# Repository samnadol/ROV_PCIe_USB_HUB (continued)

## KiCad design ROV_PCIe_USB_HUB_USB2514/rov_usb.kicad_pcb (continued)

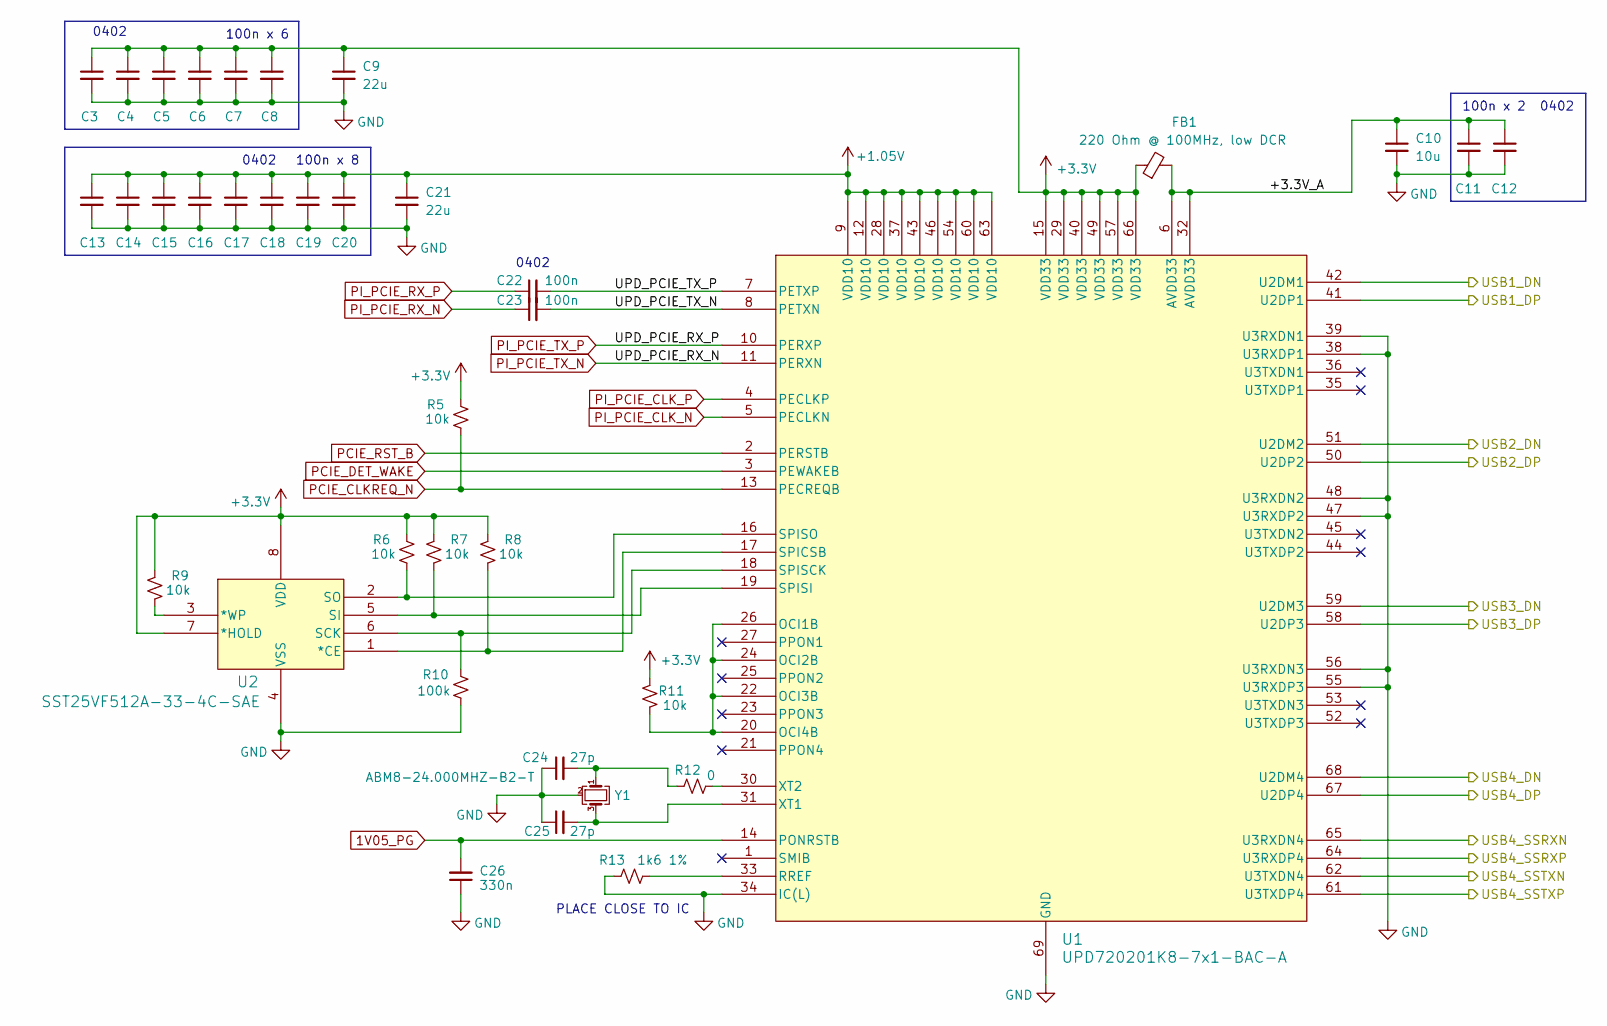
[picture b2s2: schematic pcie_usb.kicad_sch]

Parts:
C3, C4, C5, C6, C7, C8, C11, C12, C13, C14, C15, C16, C17, C18, C19, C20, C22, C23: 100n; C_0402_1005Metric; Part Number CC0402KRX7R8BB104
C9, C21: 22u; C_1206_3216Metric; Part Number CC1206KKX5R8BB226
C10: 10u; C_0805_2012Metric; Part Number CC0805KRX5R8BB106
C24, C25: 27p; C_0402_1005Metric; Part Number CC0402JRNPO9BN270
C26: 330n; C_0402_1005Metric; Part Number CC0402KPX5R6BB334
FB1: 220 Ohm @ 100MHz, low DCR; L_0805_2012Metric; Part Number BLM21PG221SN1D
R5, R6, R7, R8, R9, R11: 10k; R_0603_1608Metric; Part Number RC0603FR-0710KL
R10: 100k; R_0603_1608Metric; Part Number RC0603FR-07100KL
R12: 0; R_0402_1005Metric; Part Number RC0402JR-070RL
R13: 1k6 1%; R_0603_1608Metric; Part Number RC0603FR-071K6L
U1: UPD720201K8-7x1-BAC-A; QFN-68-1EP_8x8mm_P0.4mm_EP6.2x6.2mm
U2: SST25VF512A-33-4C-SAE; SOIC-8_3.9x4.9mm_P1.27mm
Y1: ABM8-24.000MHZ-B2-T; Crystal_SMD_3225-4Pin_3.2x2.5mm; Part Number ABM8-24.000MHZ-B2-T

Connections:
1V05_PG: C26.2, U1.14 (PONRSTB); also elsewhere on the board
+1.05V: C13.1, C14.1, C15.1, C16.1, C17.1, C18.1, C19.1, C20.1, C21.1, U1.9 (VDD10), U1.12 (VDD10), U1.28 (VDD10), U1.37 (VDD10), U1.43 (VDD10), U1.46 (VDD10), U1.54 (VDD10), U1.60 (VDD10), U1.63 (VDD10); also elsewhere on the board
+3.3V: C3.1, C4.1, C5.1, C6.1, C7.1, C8.1, C9.1, FB1.1, R5.1, R6.1, R7.1, R8.1, R9.1, R11.1, U1.15 (VDD33), U1.29 (VDD33), U1.40 (VDD33), U1.49 (VDD33), U1.57 (VDD33), U1.66 (VDD33), U2.7 (*HOLD), U2.8 (VDD); also elsewhere on the board
/PCIe_USB/+3.3V_A: C10.1, C11.1, C12.1, FB1.2, U1.6 (AVDD33), U1.32 (AVDD33)
/PCIe_USB/UPD_PCIE_TX_N: C23.2, U1.8 (PETXN)
/PCIe_USB/UPD_PCIE_TX_P: C22.2, U1.7 (PETXP)
/PCIe_USB/USB1_DN: U1.42 (U2DM1); also elsewhere on the board
/PCIe_USB/USB1_DP: U1.41 (U2DP1); also elsewhere on the board
/PCIe_USB/USB2_DN: U1.51 (U2DM2); also elsewhere on the board
/PCIe_USB/USB2_DP: U1.50 (U2DP2); also elsewhere on the board
/PCIe_USB/USB3_DN: U1.59 (U2DM3); also elsewhere on the board
/PCIe_USB/USB3_DP: U1.58 (U2DP3); also elsewhere on the board
/PCIe_USB/USB4_DN: U1.68 (U2DM4); also elsewhere on the board
/PCIe_USB/USB4_DP: U1.67 (U2DP4); also elsewhere on the board
/PCIe_USB/USB4_SSRXN: U1.65 (U3RXDN4); also elsewhere on the board
/PCIe_USB/USB4_SSRXP: U1.64 (U3RXDP4); also elsewhere on the board
/PCIe_USB/USB4_SSTXN: U1.62 (U3TXDN4); also elsewhere on the board
/PCIe_USB/USB4_SSTXP: U1.61 (U3TXDP4); also elsewhere on the board
GND: C3.2, C4.2, C5.2, C6.2, C7.2, C8.2, C9.2, C10.2, C11.2, C12.2, C13.2, C14.2, C15.2, C16.2, C17.2, C18.2, C19.2, C20.2, C21.2, C24.1, C25.1, C26.1, R10.2, R13.1, U1.34 (IC(L)), U1.38 (U3RXDP1), U1.39 (U3RXDN1), U1.47 (U3RXDP2), U1.48 (U3RXDN2), U1.55 (U3RXDP3), U1.56 (U3RXDN3), U1.69 (GND), U2.4 (VSS), Y1.2 (G), Y1.4 (G); also elsewhere on the board
unnamed: C24.2, R12.1, Y1.1
unnamed: R11.2, U1.20 (OCI4B), U1.22 (OCI3B), U1.24 (OCI2B), U1.26 (OCI1B)
unnamed: R13.2, U1.33 (RREF)
unnamed: R8.2, U1.17 (SPICSB), U2.1 (*CE)
unnamed: R10.1, U1.18 (SPISCK), U2.6 (SCK)
unnamed: R7.2, U1.19 (SPISI), U2.5 (SI)
unnamed: R6.2, U1.16 (SPISO), U2.2 (SO)
unnamed: C25.2, U1.31 (XT1), Y1.3
unnamed: R12.2, U1.30 (XT2)
unnamed: R9.2, U2.3 (*WP)
PCIE_CLKREQ_N: R5.2, U1.13 (PECREQB); also elsewhere on the board
PCIE_DET_WAKE: U1.3 (PEWAKEB); also elsewhere on the board
PCIE_RST_B: U1.2 (PERSTB); also elsewhere on the board
PI_PCIE_CLK_N: U1.5 (PECLKN); also elsewhere on the board
PI_PCIE_CLK_P: U1.4 (PECLKP); also elsewhere on the board
PI_PCIE_RX_N: C23.1; also elsewhere on the board
PI_PCIE_RX_P: C22.1; also elsewhere on the board
PI_PCIE_TX_N: U1.11 (PERXN); also elsewhere on the board
PI_PCIE_TX_P: U1.10 (PERXP); also elsewhere on the board

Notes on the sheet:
0402
100n x 6
100n x 2
PLACE CLOSE TO IC
100n x 8

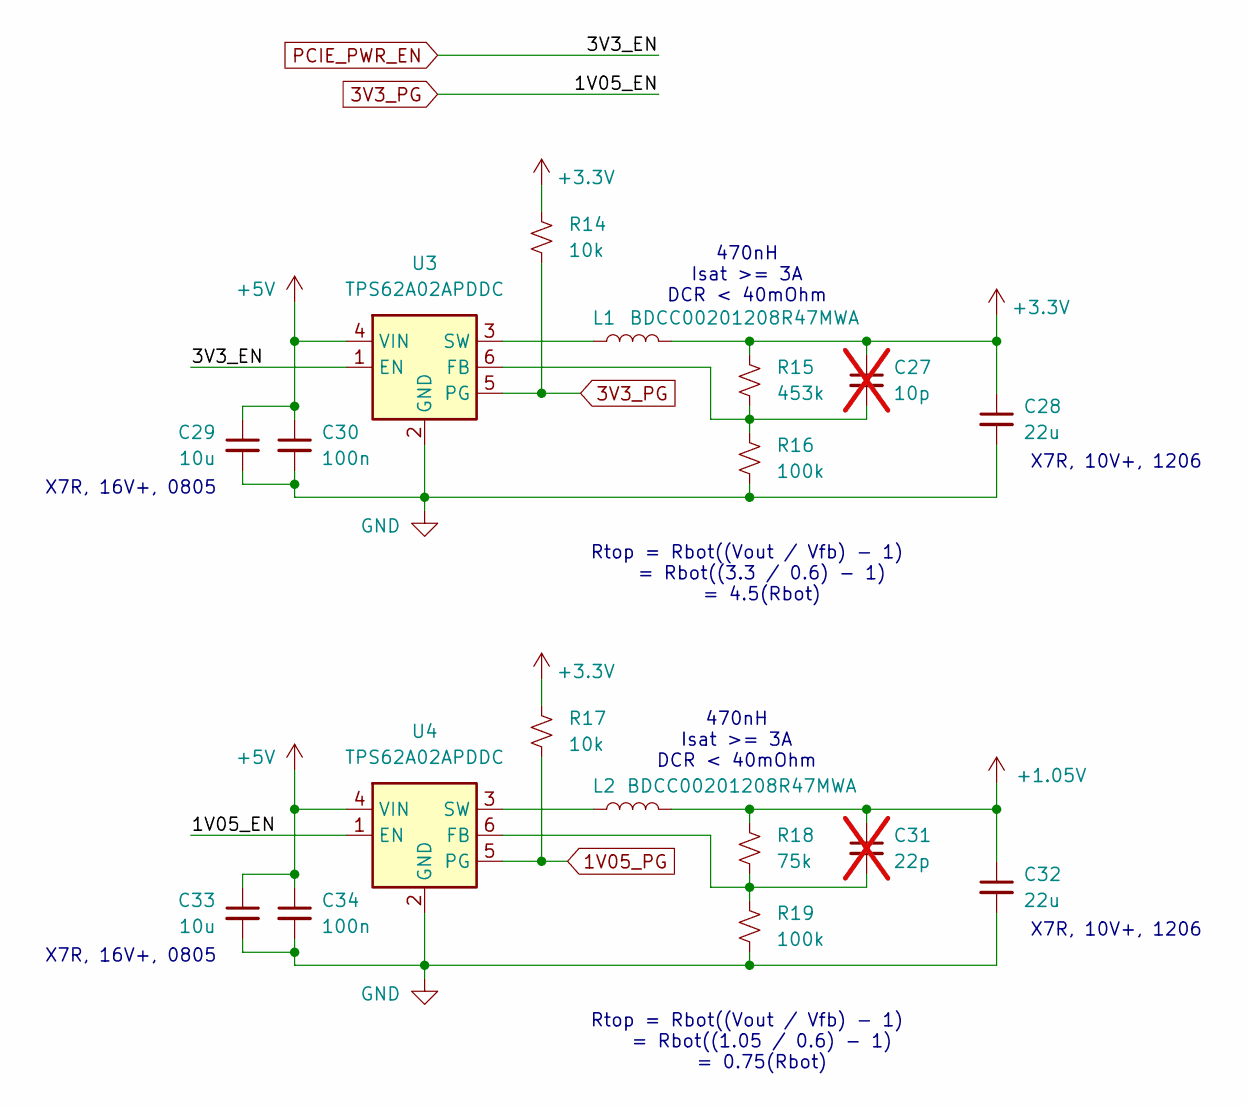
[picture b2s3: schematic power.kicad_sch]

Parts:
C27: 10p; C_0402_1005Metric; Part Number CL05C100JB5NNNC; not fitted
C28, C32: 22u; C_1206_3216Metric; Part Number CC1206KKX5R8BB226
C29, C33: 10u; C_0805_2012Metric; Part Number CC0805KRX5R8BB106
C30, C34: 100n; C_0402_1005Metric; Part Number CC0402KRX7R8BB104
C31: 22p; C_0402_1005Metric; Part Number CL05C220JB5NNNC; not fitted
L1, L2: BDCC00201208R47MWA; L_0805_2012Metric; Part Number BDCC00201208R47MWA
R14, R17: 10k; R_0603_1608Metric; Part Number RC0603FR-0710KL
R15: 453k; R_0603_1608Metric; Part Number RC0603FR-07453KL
R16, R19: 100k; R_0603_1608Metric; Part Number RC0603FR-07100KL
R18: 75k; R_0603_1608Metric; Part Number RC0603FR-0775KL
U3, U4: TPS62A02APDDC; SOT-23-6; Part Number TPS62A02APDDC

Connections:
1V05_PG: R17.2, U4.5 (PG); also elsewhere on the board
3V3_PG: R14.2, U3.5 (PG), U4.1 (EN)
+1.05V: C31.1, C32.1, L2.2, R18.1; also elsewhere on the board
+3.3V: C27.1, C28.1, L1.2, R14.1, R15.1, R17.1; also elsewhere on the board
+5V: C29.1, C30.1, C33.1, C34.1, U3.4 (VIN), U4.4 (VIN); also elsewhere on the board
GND: C28.2, C29.2, C30.2, C32.2, C33.2, C34.2, R16.2, R19.2, U3.2 (GND), U4.2 (GND); also elsewhere on the board
unnamed: C27.2, R15.2, R16.1, U3.6 (FB)
unnamed: L1.1, U3.3 (SW)
unnamed: C31.2, R18.2, R19.1, U4.6 (FB)
unnamed: L2.1, U4.3 (SW)
PCIE_PWR_EN: U3.1 (EN); also elsewhere on the board

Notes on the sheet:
X7R, 10V+, 1206
470nH Isat >= 3A DCR < 40mOhm
X7R, 16V+, 0805
Rtop = Rbot((Vout / Vfb) - 1) = Rbot((3.3 / 0.6) - 1) = 4.5(Rbot)
Rtop = Rbot((Vout / Vfb) - 1) = Rbot((1.05 / 0.6) - 1) = 0.75(Rbot)

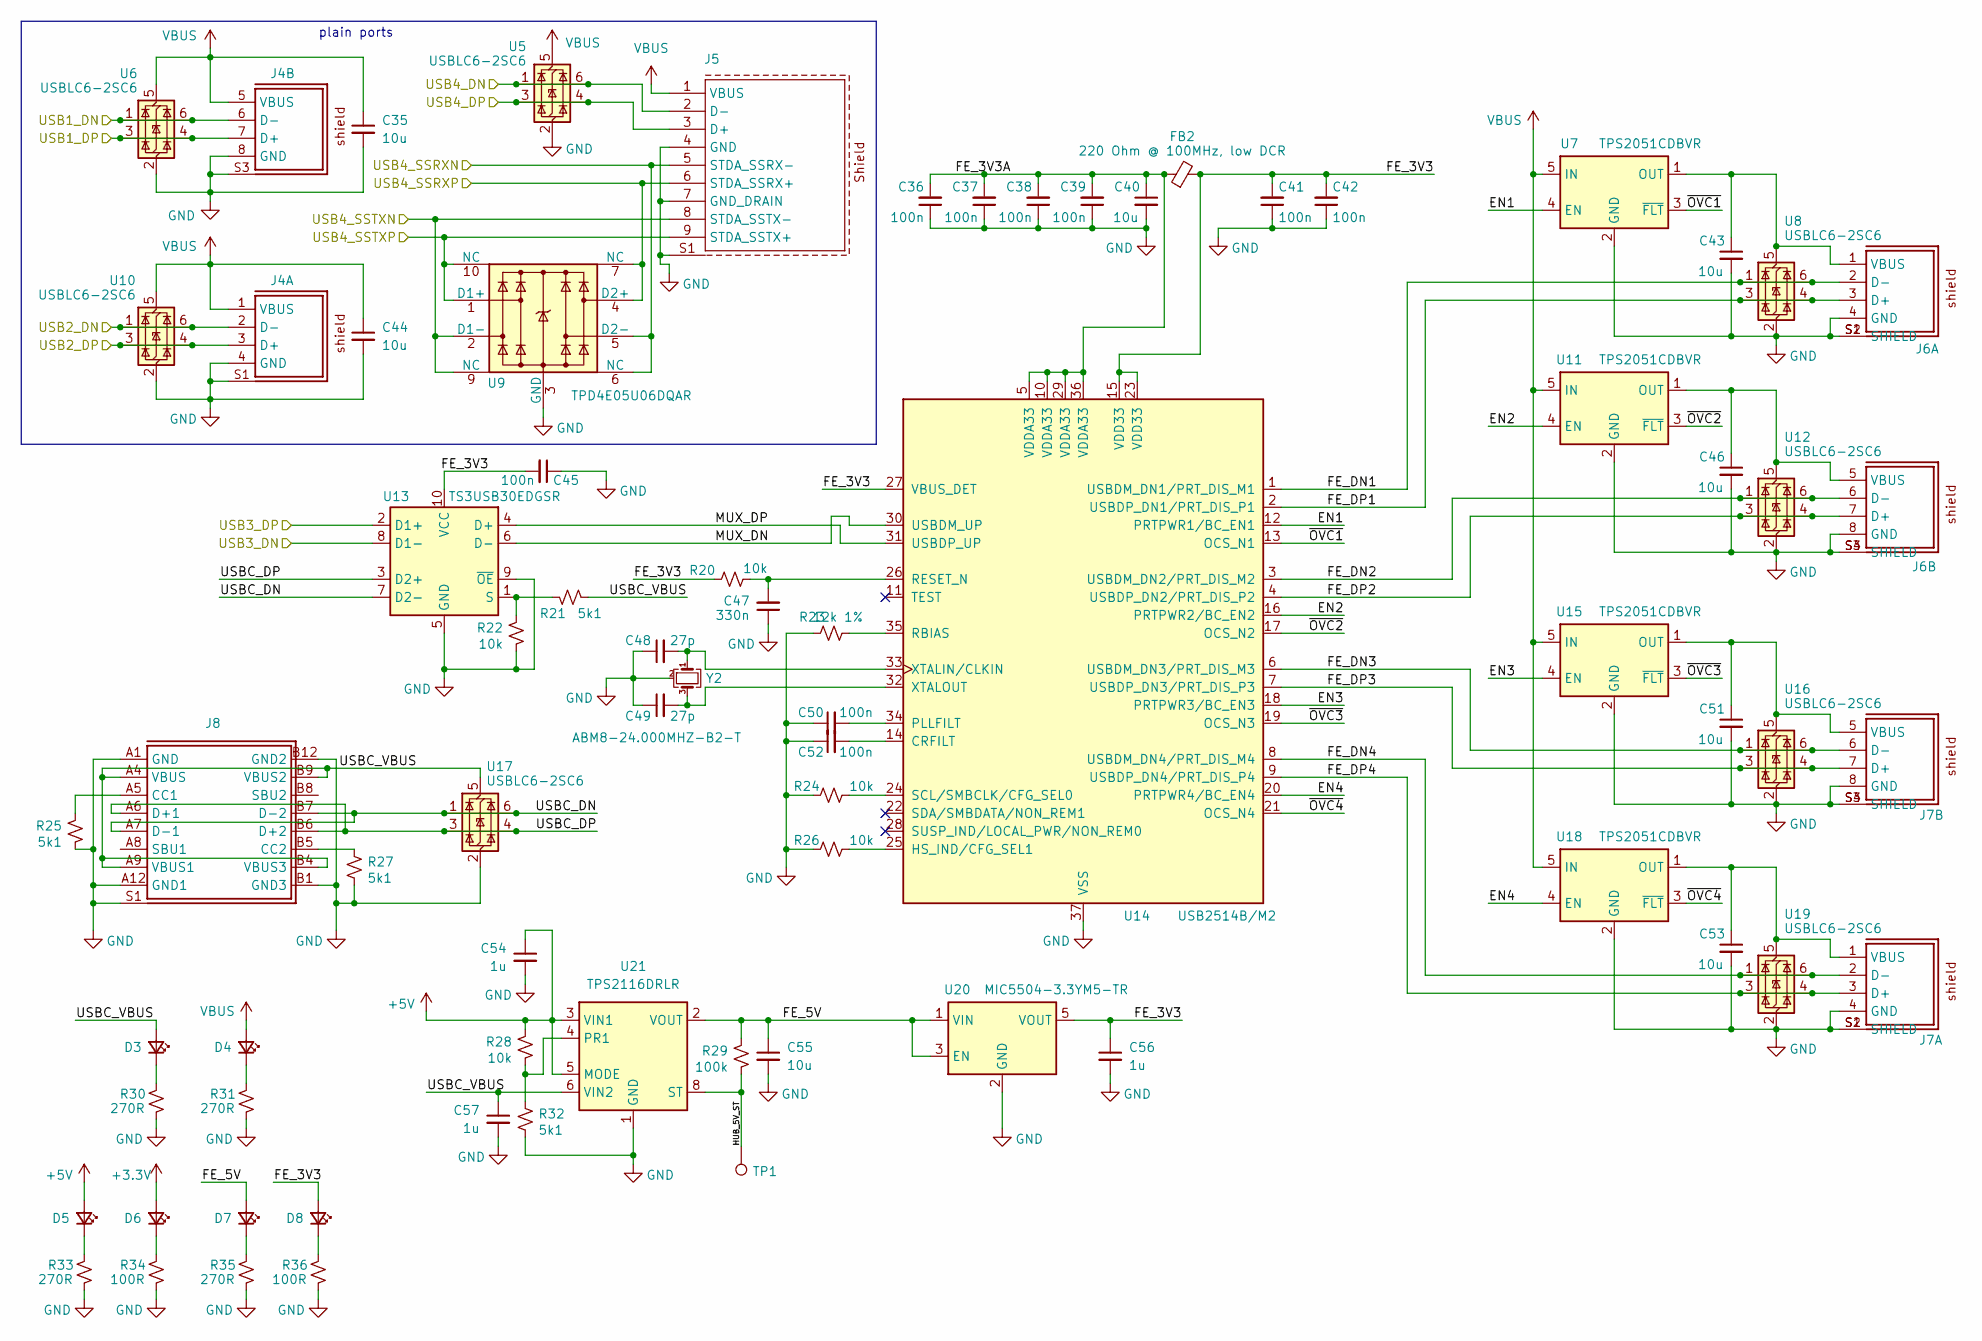
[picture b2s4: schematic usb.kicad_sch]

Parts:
C35, C40, C43, C44, C46, C51, C53, C55: 10u; C_0805_2012Metric; Part Number CC0805KRX5R8BB106
C36, C37, C38, C39, C41, C42, C45, C50, C52: 100n; C_0402_1005Metric; Part Number CC0402KRX7R8BB104
C47: 330n; C_0402_1005Metric; Part Number CC0402KPX5R6BB334
C48, C49: 27p; C_0402_1005Metric; Part Number CC0402JRNPO9BN270
C54, C56, C57: 1u; C_0603_1608Metric; Part Number CC0603KRX7R8BB105
D3, D4, D5, D6, D7, D8: Green; LED_0603_1608Metric; Part Number LTST-C190KGKT
FB2: 220 Ohm @ 100MHz, low DCR; L_0805_2012Metric; Part Number BLM21PG221SN1D
J4, J6, J7: USB-A-D-RA; J_Wurth_WR-USB_61400826021; Working Voltage (V (AC)) 30; Part Number USB-A-D-RA
J5: USB-A3-S-VT-CS5A; J_Wurth_WR-USB_692121430000; Working Voltage(V (AC)) 30 V (AC); Part Number USB-A3-S-VT-CS5A
J8: USB4085-GF-A; J_Wurth_WR-USB_629722000214; Working Voltage (V (AC)) 20; Part Number USB4085-GF-A
R20, R22, R24, R26, R28: 10k; R_0603_1608Metric; Part Number RC0603FR-0710KL
R21, R25, R27, R32: 5k1; R_0603_1608Metric; Part Number RC0603FR-075K1L
R23: 12k 1%; R_0603_1608Metric; Part Number RC0603FR-0712KL
R29: 100k; R_0603_1608Metric; Part Number RC0603FR-07100KL
R30, R31, R33, R35: 270R; R_0603_1608Metric; Part Number RC0603FR-07270RL
R34, R36: 100R; R_0603_1608Metric; Part Number RC0603FR-07100RL
TP1: TestPoint; TestPoint_Pad_1.0x1.0mm
U5, U6, U8, U10, U12, U16, U17, U19: USBLC6-2SC6; SOT-23-6; Part Number USBLC6-2SC6
U7, U11, U15, U18: TPS2051CDBVR; SOT-23-5; Part Number TPS2051CDBVR
U9: TPD4E05U06DQAR; USON-10_2.5x1.0mm_P0.5mm; Part Number TPD4E05U06DQAR
U13: TS3USB30EDGSR; TSSOP-10_3x3mm_P0.5mm; Part Number TS3USB30EDGSR
U14: USB2514B/M2; QFN-36-1EP_6x6mm_P0.5mm_EP3.7x3.7mm; Part Number USB2514B/M2
U20: MIC5504-3.3YM5-TR; SOT-23-5; Part Number MIC5504-3.3YM5-TR
U21: TPS2116DRLR; SOT-583-8; Part Number TPS2116DRLR
Y2: ABM8-24.000MHZ-B2-T; Crystal_SMD_3225-4Pin_3.2x2.5mm; Part Number ABM8-24.000MHZ-B2-T

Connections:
+3.3V: D6.2 (A); also elsewhere on the board
+5V: C54.1, D5.2 (A), R28.2, U21.3 (VIN1), U21.5 (MODE); also elsewhere on the board
/PCIe_USB/USB1_DN: J4.6 (D-), U6.1 (I/O1), U6.6 (I/O1); also elsewhere on the board
/PCIe_USB/USB1_DP: J4.7 (D+), U6.3 (I/O2), U6.4 (I/O2); also elsewhere on the board
/PCIe_USB/USB2_DN: J4.2 (D-), U10.1 (I/O1), U10.6 (I/O1); also elsewhere on the board
/PCIe_USB/USB2_DP: J4.3 (D+), U10.3 (I/O2), U10.4 (I/O2); also elsewhere on the board
/PCIe_USB/USB3_DN: U13.8 (D1-); also elsewhere on the board
/PCIe_USB/USB3_DP: U13.2 (D1+); also elsewhere on the board
/PCIe_USB/USB4_DN: J5.2 (D-), U5.1 (I/O1), U5.6 (I/O1); also elsewhere on the board
/PCIe_USB/USB4_DP: J5.3 (D+), U5.3 (I/O2), U5.4 (I/O2); also elsewhere on the board
/PCIe_USB/USB4_SSRXN: J5.5 (STDA_SSRX-), U9.5 (D2-), U9.6 (NC); also elsewhere on the board
/PCIe_USB/USB4_SSRXP: J5.6 (STDA_SSRX+), U9.4 (D2+), U9.7 (NC); also elsewhere on the board
/USB/EN1: U7.4 (EN), U14.12 (PRTPWR1/BC_EN1)
/USB/EN2: U11.4 (EN), U14.16 (PRTPWR2/BC_EN2)
/USB/EN3: U14.18 (PRTPWR3/BC_EN3), U15.4 (EN)
/USB/EN4: U14.20 (PRTPWR4/BC_EN4), U18.4 (EN)
/USB/FE_3V3: C41.2, C42.2, C45.2, C56.1, D8.2 (A), FB2.2, R20.2, U13.10 (VCC), U14.15 (VDD33), U14.23 (VDD33), U14.27 (VBUS_DET), U20.5 (VOUT)
/USB/FE_3V3A: C36.2, C37.2, C38.2, C39.2, C40.1, FB2.1, U14.5 (VDDA33), U14.10 (VDDA33), U14.29 (VDDA33), U14.36 (VDDA33)
/USB/FE_5V: C55.1, D7.2 (A), R29.2, U20.1 (VIN), U20.3 (EN), U21.2 (VOUT), U21.7 (VOUT)
/USB/FE_DN1: J6.2 (D-), U8.1 (I/O1), U8.6 (I/O1), U14.1 (USBDM_DN1/PRT_DIS_M1)
/USB/FE_DN2: J6.6 (D-), U12.1 (I/O1), U12.6 (I/O1), U14.3 (USBDM_DN2/PRT_DIS_M2)
/USB/FE_DN3: J7.6 (D-), U14.6 (USBDM_DN3/PRT_DIS_M3), U16.1 (I/O1), U16.6 (I/O1)
/USB/FE_DN4: J7.2 (D-), U14.8 (USBDM_DN4/PRT_DIS_M4), U19.1 (I/O1), U19.6 (I/O1)
/USB/FE_DP1: J6.3 (D+), U8.3 (I/O2), U8.4 (I/O2), U14.2 (USBDP_DN1/PRT_DIS_P1)
/USB/FE_DP2: J6.7 (D+), U12.3 (I/O2), U12.4 (I/O2), U14.4 (USBDP_DN2/PRT_DIS_P2)
/USB/FE_DP3: J7.7 (D+), U14.7 (USBDP_DN3/PRT_DIS_P3), U16.3 (I/O2), U16.4 (I/O2)
/USB/FE_DP4: J7.3 (D+), U14.9 (USBDP_DN4/PRT_DIS_P4), U19.3 (I/O2), U19.4 (I/O2)
/USB/HUB_5V_ST: R29.1, TP1.1 (1_1), U21.8 (ST)
/USB/MUX_DN: U13.6 (D-), U14.30 (USBDM_UP)
/USB/MUX_DP: U13.4 (D+), U14.31 (USBDP_UP)
/USB/USB4_SSTXN: J5.8 (STDA_SSTX-), U9.2 (D1-), U9.9 (NC); also elsewhere on the board
/USB/USB4_SSTXP: J5.9 (STDA_SSTX+), U9.1 (D1+), U9.10 (NC); also elsewhere on the board
/USB/USBC_DN: J8.A7 (D-1), J8.B7 (D-2), U13.7 (D2-), U17.1 (I/O1), U17.6 (I/O1)
/USB/USBC_DP: J8.A6 (D+1), J8.B6 (D+2), U13.3 (D2+), U17.3 (I/O2), U17.4 (I/O2)
/USB/USBC_VBUS: C57.1, D3.2 (A), J8.A4 (VBUS), J8.A9 (VBUS1), J8.B4 (VBUS3), J8.B9 (VBUS2), R21.1, U17.5 (VBUS), U21.6 (VIN2)
/USB/~OVC1: U7.3 (~FLT), U14.13 (OCS_N1)
/USB/~OVC2: U11.3 (~FLT), U14.17 (OCS_N2)
/USB/~OVC3: U14.19 (OCS_N3), U15.3 (~FLT)
/USB/~OVC4: U14.21 (OCS_N4), U18.3 (~FLT)
GND: C35.2, C36.1, C37.1, C38.1, C39.1, C40.2, C41.1, C42.1, C43.2, C44.2, C45.1, C46.2, C47.1, C48.1, C49.1, C50.1, C51.2, C52.1, C53.2, C54.2, C55.2, C56.2, C57.2, J4.4 (GND), J4.8 (GND), J4.S1, J4.S2, J4.S3, J4.S4, J5.4 (GND), J5.7 (GND_DRAIN), J5.S1, J5.S2 (SHIELD), J6.4 (GND), J6.8 (GND), J6.S1 (SHIELD), J6.S2 (SHIELD), J6.S3 (SHIELD), J6.S4 (SHIELD), J7.4 (GND), J7.8 (GND), J7.S1 (SHIELD), J7.S2 (SHIELD), J7.S3 (SHIELD), J7.S4 (SHIELD), J8.A1 (GND), J8.A12 (GND1), J8.B1 (GND3), J8.B12 (GND2), J8.S1, J8.S2, J8.S3, J8.S4, R22.1, R23.2, R24.2, R25.1, R26.2, R27.1, R30.1, R31.1, R32.1, R33.1, R34.1, R35.1, R36.1, U5.2 (GND), U6.2 (GND), U7.2 (GND), U8.2 (GND), U9.3 (GND), U9.8 (GND), U10.2 (GND), U11.2 (GND), U12.2 (GND), U13.5 (GND), U13.9 (~OE), U14.37 (VSS), U15.2 (GND), U16.2 (GND), U17.2 (GND), U18.2 (GND), U19.2 (GND), U20.2 (GND), U21.1 (GND), Y2.2 (G), Y2.4 (G); also elsewhere on the board
unnamed: D3.1 (K), R30.2
unnamed: D4.1 (K), R31.2
unnamed: D5.1 (K), R33.2
unnamed: D6.1 (K), R34.2
unnamed: D7.1 (K), R35.2
unnamed: D8.1 (K), R36.2
unnamed: C43.1, J6.1 (VBUS), U7.1 (OUT), U8.5 (VBUS)
unnamed: C46.1, J6.5 (VBUS), U11.1 (OUT), U12.5 (VBUS)
unnamed: C53.1, J7.1 (VBUS), U18.1 (OUT), U19.5 (VBUS)
unnamed: C51.1, J7.5 (VBUS), U15.1 (OUT), U16.5 (VBUS)
unnamed: J8.A5 (CC1), R25.2
unnamed: J8.B5 (CC2), R27.2
unnamed: R21.2, R22.2, U13.1 (S)
unnamed: C52.2, U14.14 (CRFILT)
unnamed: R26.1, U14.25 (HS_IND/CFG_SEL1)
unnamed: C50.2, U14.34 (PLLFILT)
unnamed: R23.1, U14.35 (RBIAS)
unnamed: C47.2, R20.1, U14.26 (RESET_N)
unnamed: R24.1, U14.24 (SCL/SMBCLK/CFG_SEL0)
unnamed: C48.2, U14.33 (XTALIN/CLKIN), Y2.1
unnamed: C49.2, U14.32 (XTALOUT), Y2.3
unnamed: R28.1, R32.2, U21.4 (PR1)
VBUS: C35.1, C44.1, D4.2 (A), J4.1 (VBUS), J4.5 (VBUS), J5.1 (VBUS), U5.5 (VBUS), U6.5 (VBUS), U7.5 (IN), U10.5 (VBUS), U11.5 (IN), U15.5 (IN), U18.5 (IN); also elsewhere on the board

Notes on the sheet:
plain ports

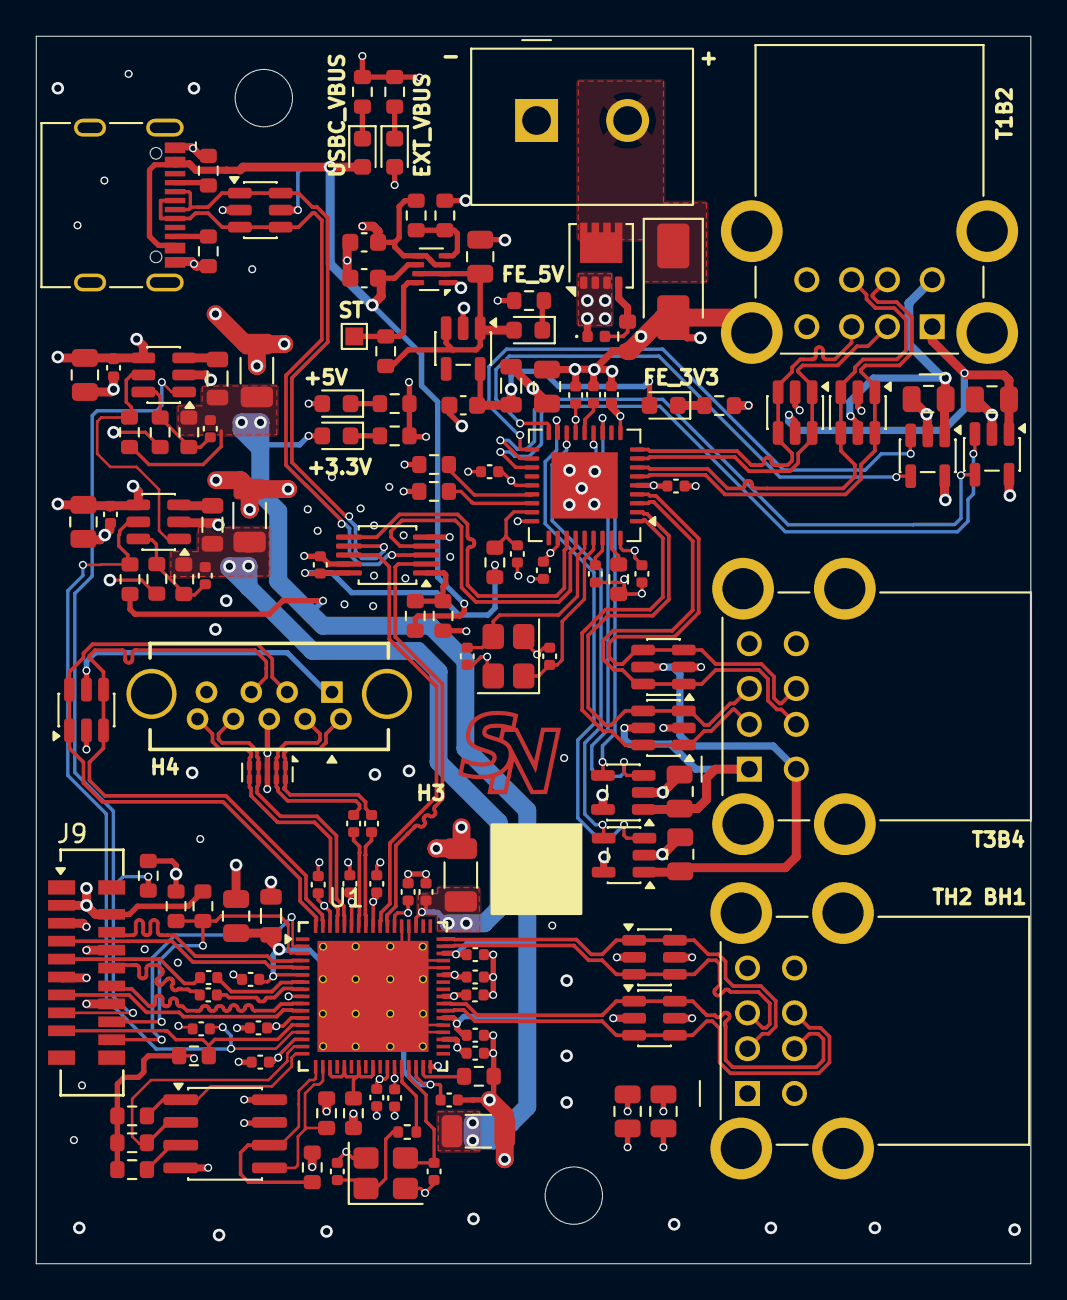
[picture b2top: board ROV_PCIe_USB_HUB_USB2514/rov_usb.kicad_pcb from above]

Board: 4 copper layers, 55.5 x 68.5 mm, 139 parts (0 on the bottom side), 97 nets.

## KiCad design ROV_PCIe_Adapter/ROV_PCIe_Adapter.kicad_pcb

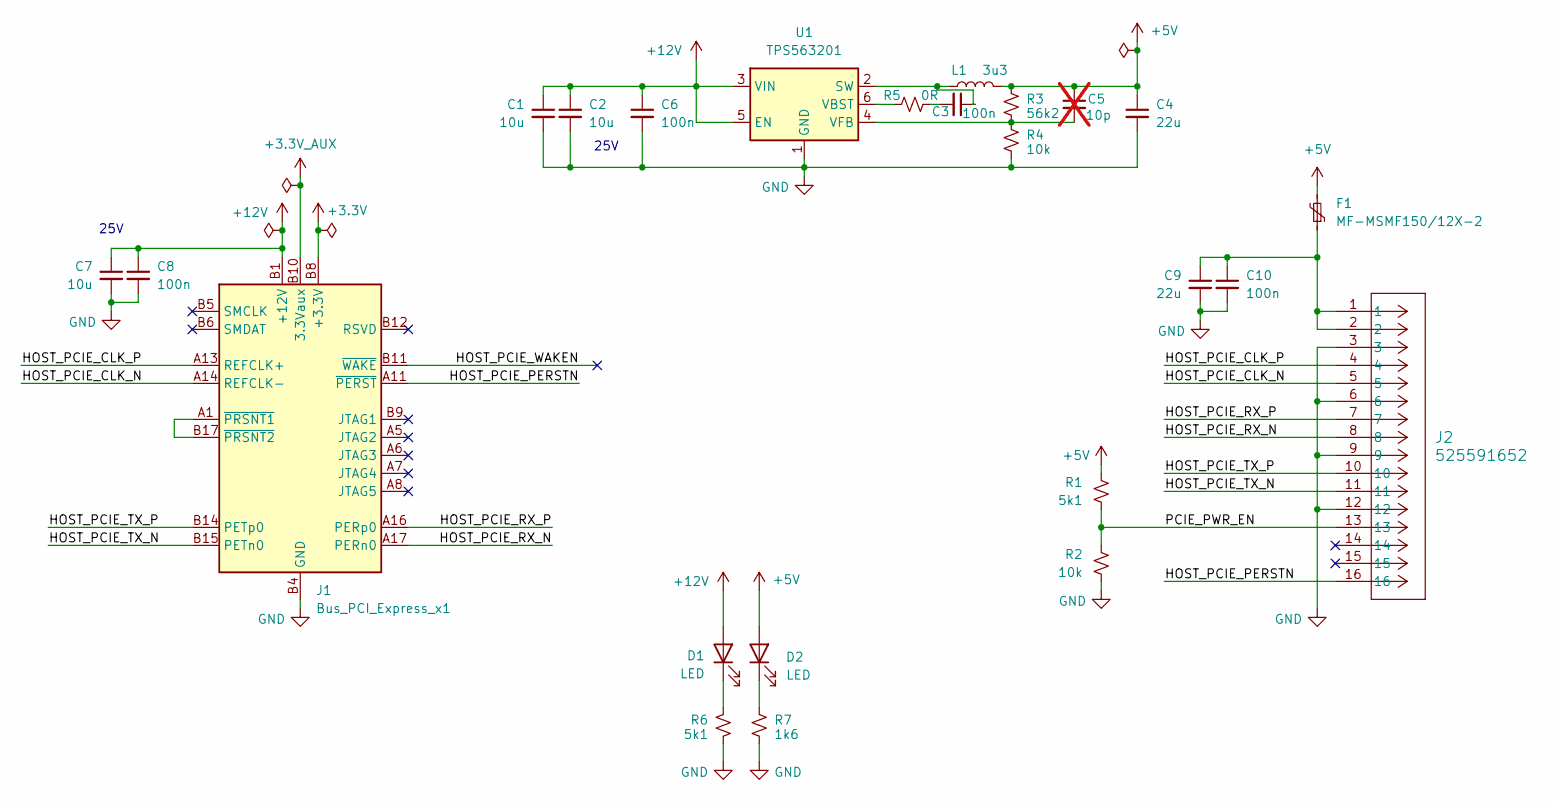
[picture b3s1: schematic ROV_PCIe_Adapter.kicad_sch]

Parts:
C1, C2, C7: 10u; C_0805_2012Metric; Voltage Rating 25; Part Number CC0805KRX5R8BB106
C3, C6, C8, C10: 100n; C_0402_1005Metric; Voltage Rating 25; Part Number CC0402KRX7R8BB104
C4, C9: 22u; C_1206_3216Metric; Voltage Rating 25; Part Number CC1206KKX5R8BB226
C5: 10p; C_0402_1005Metric; Part Number CL05A104KA5NNNC; not fitted
D1, D2: LED; LED_0603_1608Metric; Part Number LTST-C190KGKT
F1: MF-MSMF150/12X-2; Fuse_1812_4532Metric; Part Number MF-MSMF150/12X-2
J1: Bus_PCI_Express_x1; BUS_PCIexpress_x1
J2: 525591652; Part Number 525591652
L1: 3u3; L_Taiyo-Yuden_MD-5050; Part Number BWVC005050403R3M00
R1, R6: 5k1; R_0603_1608Metric; Part Number RC0603FR-075K1L
R2, R4: 10k; R_0603_1608Metric; Part Number RC0603FR-0710KL
R3: 56k2; R_0603_1608Metric; Part Number RC0603FR-0756K2L
R5: 0R; R_0402_1005Metric; Part Number RC0402JR-070RL
R7: 1k6; R_0603_1608Metric; Part Number RC0603FR-071K6L
U1: TPS563201; SOT-23-6; Part Number TPS563201DDCR

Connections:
+3.3V: J1.A9 (+3.3V), J1.A10 (+3.3V), J1.B8 (+3.3V)
+3.3V_AUX: J1.B10 (3.3Vaux)
+5V: C4.1, C5.1, D2.2 (A), F1.2, L1.2, R1.1, R3.1
+12V: C1.1, C2.1, C6.1, C7.1, C8.1, D1.2 (A), J1.A2 (+12V), J1.A3 (+12V), J1.B1 (+12V), J1.B2 (+12V), J1.B3 (+12V), U1.3 (VIN), U1.5 (EN)
/HOST_PCIE_CLK_N: J1.A14 (REFCLK-), J2.5
/HOST_PCIE_CLK_P: J1.A13 (REFCLK+), J2.4
/HOST_PCIE_PERSTN: J1.A11 (~PERST), J2.16
/HOST_PCIE_RX_N: J1.A17 (PERn0), J2.8
/HOST_PCIE_RX_P: J1.A16 (PERp0), J2.7
/HOST_PCIE_TX_N: J1.B15 (PETn0), J2.11
/HOST_PCIE_TX_P: J1.B14 (PETp0), J2.10
/HOST_PCIE_WAKEN: J1.B11 (~WAKE)
/PCIE_PWR_EN: J2.13, R1.2, R2.1
GND: C1.2, C2.2, C4.2, C6.2, C7.2, C8.2, C9.2, C10.2, J1.A4 (GND), J1.A12 (GND), J1.A15 (GND), J1.A18 (GND), J1.B4 (GND), J1.B7 (GND), J1.B13 (GND), J1.B16 (GND), J1.B18 (GND), J2.3, J2.6, J2.9, J2.12, R2.2, R4.2, R6.2, R7.2, U1.1 (GND)
unnamed: C3.2, R5.2
unnamed: C9.1, C10.1, F1.1, J2.1, J2.2
unnamed: D1.1 (K), R6.1
unnamed: D2.1 (K), R7.1
unnamed: J1.A1 (~PRSNT1), J1.B17 (~PRSNT2)
unnamed: C3.1, L1.1, U1.2 (SW)
unnamed: R5.1, U1.6 (VBST)
unnamed: C5.2, R3.2, R4.1, U1.4 (VFB)

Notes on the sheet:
25V

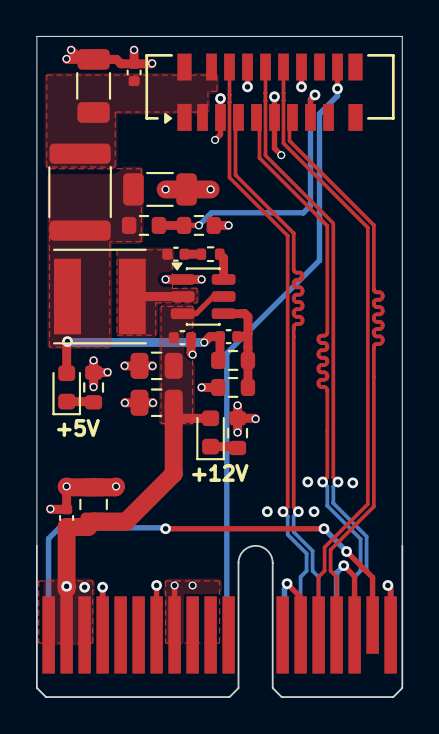
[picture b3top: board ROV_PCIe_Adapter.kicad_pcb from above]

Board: 4 copper layers, 20.3 x 36.7 mm, 24 parts (0 on the bottom side), 20 nets.

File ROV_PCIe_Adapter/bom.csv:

"Reference","Qty","Voltage Rating","Value","Part Number","Footprint"
"C1,C2,C7","3","25","10u","CC0805KRX5R8BB106","Capacitor_SMD:C_0805_2012Metric"
"C3,C6,C8,C10","4","25","100n","CC0402KRX7R8BB104","Capacitor_SMD:C_0402_1005Metric"
"C4,C9","2","25","22u","CC1206KKX5R8BB226","Capacitor_SMD:C_1206_3216Metric"
"F1","1","","MF-MSMF150/12X-2","MF-MSMF150/12X-2","Fuse:Fuse_1812_4532Metric"
"J2","1","","525591652","525591652","snadol:525591652"
"L1","1","","3u3","BWVC005050403R3M00","Inductor_SMD:L_Taiyo-Yuden_MD-5050"
"R1","1","","5k1","RC0603FR-075K1L","Resistor_SMD:R_0603_1608Metric"
"R2,R4","2","","10k","RC0603FR-0710KL","Resistor_SMD:R_0603_1608Metric"
"R3","1","","56k2","RC0603FR-0756K2L","Resistor_SMD:R_0603_1608Metric"
"R5","1","","0R","RC0402JR-070RL","Resistor_SMD:R_0402_1005Metric"
"U1","1","","TPS563201","TPS563201DDCR","Package_TO_SOT_SMD:SOT-23-6"

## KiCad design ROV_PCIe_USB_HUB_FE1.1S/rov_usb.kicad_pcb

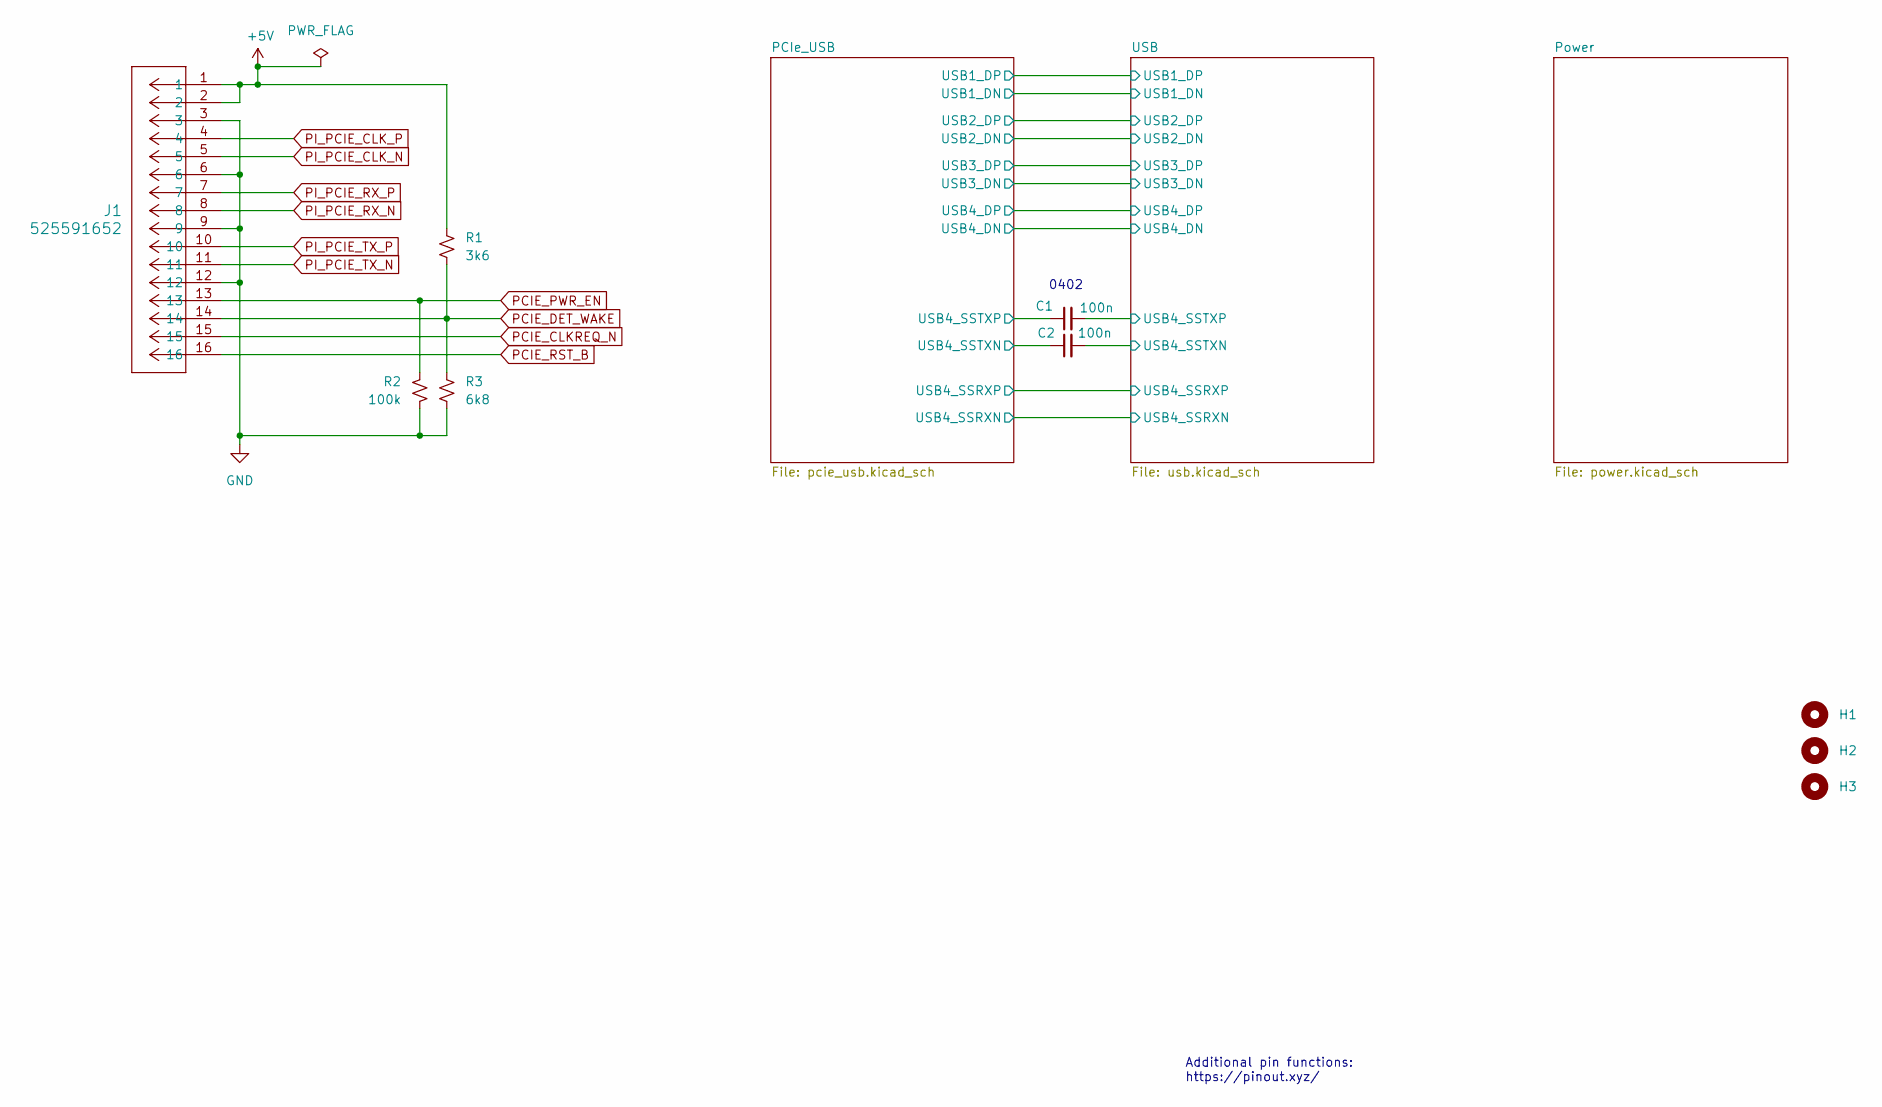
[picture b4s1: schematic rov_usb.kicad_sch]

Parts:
C1, C2: 100n; C_0402_1005Metric; Part Number CL05B104KO5NNNC
H1, H2, H3: MountingHole; MountingHole_3.2mm_M3
J1: 525591652; Part Number 525591652
R1: 3k6; R_0603_1608Metric; Part Number RC0603FR-073K6L
R2: 100k; R_0603_1608Metric; Part Number RC0603FR-07100KL
R3: 6k8; R_0603_1608Metric; Part Number RC0603FR-076K8L

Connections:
+5V: J1.1, J1.2, R1.1; also elsewhere on the board
/PCIe_USB/USB4_SSTXN: C2.1; also elsewhere on the board
/PCIe_USB/USB4_SSTXP: C1.1; also elsewhere on the board
/USB/USB4_SSTXN: C2.2; also elsewhere on the board
/USB/USB4_SSTXP: C1.2; also elsewhere on the board
GND: J1.3, J1.6, J1.9, J1.12, R2.2, R3.2; also elsewhere on the board
PCIE_CLKREQ_N: J1.15; also elsewhere on the board
PCIE_DET_WAKE: J1.14, R1.2, R3.1; also elsewhere on the board
PCIE_PWR_EN: J1.13, R2.1; also elsewhere on the board
PCIE_RST_B: J1.16; also elsewhere on the board
PI_PCIE_CLK_N: J1.5; also elsewhere on the board
PI_PCIE_CLK_P: J1.4; also elsewhere on the board
PI_PCIE_RX_N: J1.8; also elsewhere on the board
PI_PCIE_RX_P: J1.7; also elsewhere on the board
PI_PCIE_TX_N: J1.11; also elsewhere on the board
PI_PCIE_TX_P: J1.10; also elsewhere on the board

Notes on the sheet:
Additional pin functions: https://pinout.xyz/
0402
